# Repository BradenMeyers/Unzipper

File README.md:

# Unzipper 

These are the code files for the unzipper project. 
We have built a pully retreival sytem for a zipline that can autonomously bring the pulley back to the top of the zipline after a rider has got off the line.
The code runs on the Arduino framework and the platformIO build platform. 
The ESP32 is the microcontroller we are using to support this project. The ESP32 runs the program and hosts a server that you can connect to via WIFI to adjust settings on the system. 
It is built into a custom designed circuit that we use to control the motors, lights, and sensors.

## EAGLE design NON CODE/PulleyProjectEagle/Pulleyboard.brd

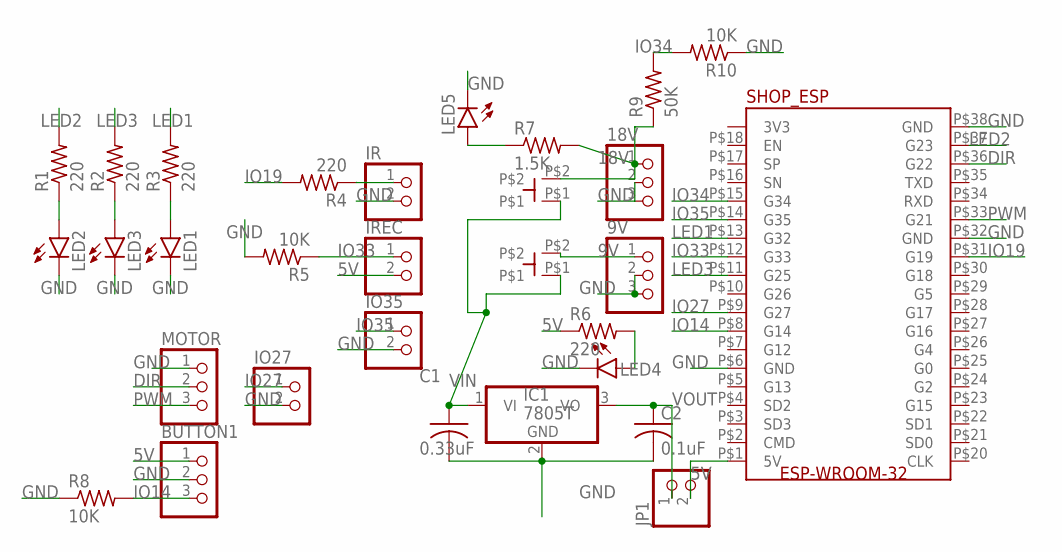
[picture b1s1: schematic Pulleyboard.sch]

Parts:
9V, 18V: PINHD-1X3; 1X03
9VSW, 18VSW: SWITCH; SWTICH
BUTTON1: PINHD-1X3; 1X03
C1: 0.33uF; C025-030X050
C2: 0.1uF; C025-030X050
IC1: 7805T; TO220H
IO27, IO35: PINHD-1X2; 1X02
IR: PINHD-1X2; 1X02
IREC: PINHD-1X2; 1X02
JP1: PINHD-1X2; 1X02
LED1, LED2, LED3, LED5: LED5MM
LED4: LEDCHIPLED_1206; CHIPLED_1206
MOTOR: PINHD-1X3; 1X03
R1, R2, R3, R4, R6: 220; R0805
R5, R8, R10: 10K; R0805
R7: 1.5K; R0805
R9: 50K; R0805
U$3: SHOP_ESP; ESP32-WROOM-32

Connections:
3V3: U$3.P$19 (3V3)
5V: BUTTON1.1, IREC.2, JP1.2, R6.1, U$3.P$1 (5V)
9V: 9V.1, 9VSW.P$2
18V: 18V.1, 18VSW.P$2, R7.2, R9.1
CMD: U$3.P$2 (CMD)
DIR: MOTOR.2, U$3.P$36 (G22)
GND: 9V.2, 9V.3, 18V.2, 18V.3, BUTTON1.2, C1.2, C2.2, IC1.2 (GND), IO27.2, IO35.2, IR.2, LED1.K (C), LED2.K (C), LED3.K (C), LED4.C, LED5.K (C), MOTOR.1, R5.2, R8.1, R10.1, U$3.P$6 (GND), U$3.P$32 (GND), U$3.P$38 (GND)
IO14: BUTTON1.3, R8.2, U$3.P$8 (G14)
IO19: R4.2, U$3.P$31 (G19)
IO27: IO27.1, U$3.P$9 (G27)
IO33: IREC.1, R5.1, U$3.P$12 (G33)
IO34: R9.2, R10.2, U$3.P$15 (G34)
IO35: IO35.1, U$3.P$14 (G35)
LED1: R3.2, U$3.P$13 (G32)
LED2: R1.2, U$3.P$37 (G23)
LED3: R2.2, U$3.P$11 (G25)
unnamed: LED2.A, R1.1
unnamed: LED3.A, R2.1
unnamed: LED1.A, R3.1
unnamed: LED5.A, R7.1
unnamed: IR.1, R4.1
unnamed: LED4.A, R6.2
PWM: MOTOR.3, U$3.P$33 (G21)
VIN: 9VSW.P$1, 18VSW.P$1, C1.1, IC1.1 (VI)
VOUT: C2.1, IC1.3 (VO), JP1.1

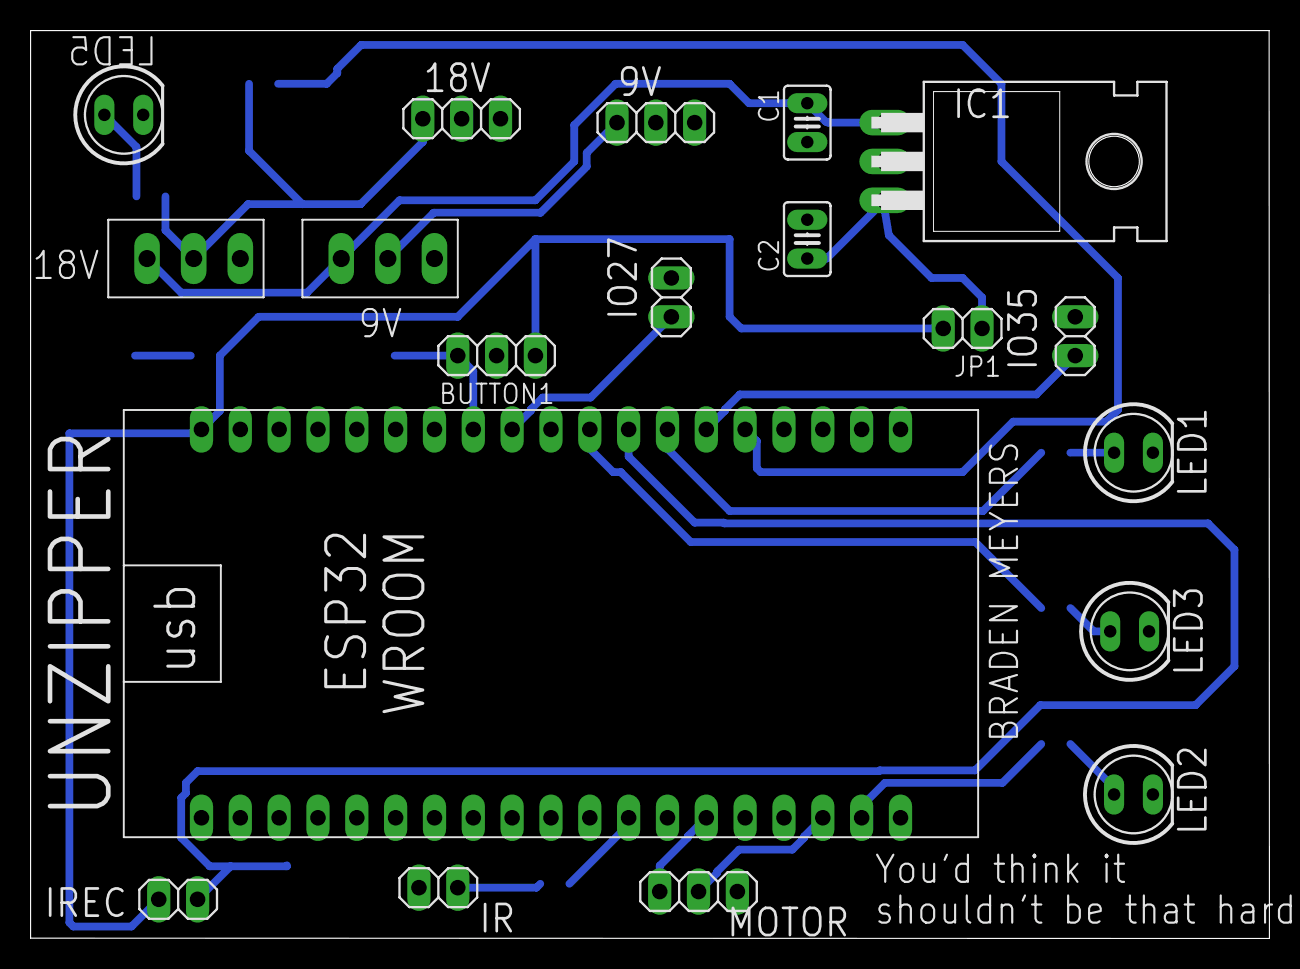
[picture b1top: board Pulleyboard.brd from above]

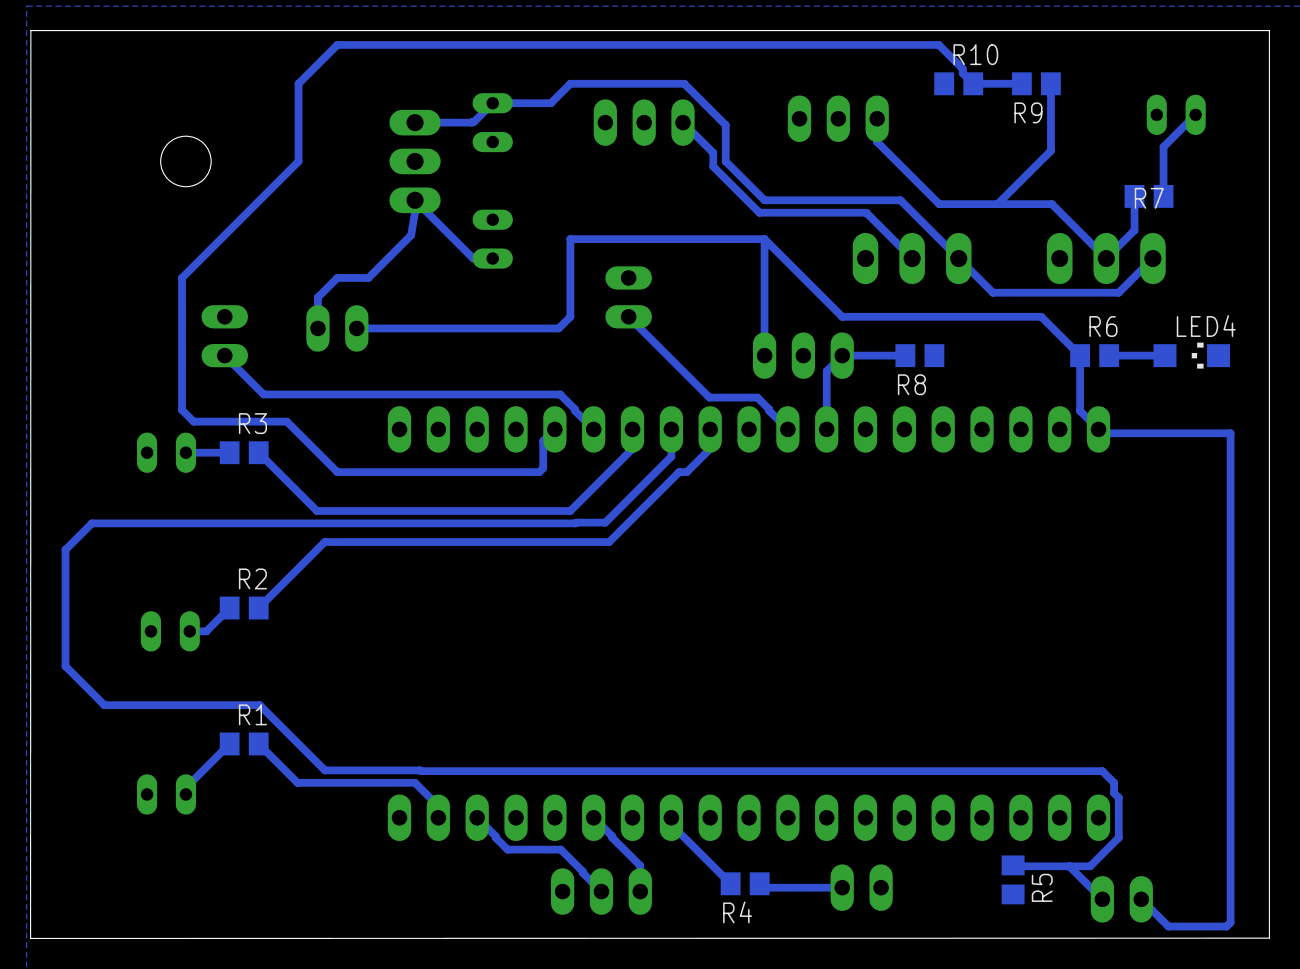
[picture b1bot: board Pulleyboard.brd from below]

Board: 2 copper layers, 81.0 x 59.4 mm, 30 parts (11 on the bottom side), 23 nets.

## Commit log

2022-11-26 Working code! Seperate files
2022-12-04 added cad files
2022-12-04 photos of cicruit board
2022-12-12 working remote controll ayay
2022-12-19 more remote functions
2022-12-22 remote with racecar mode
2023-03-14 pre website changes
2023-03-14 New Tests, Webiste, accelormeter
2023-03-17 accelerometer with Stability
2023-03-17 More server accel
2023-03-19 Servo was breaking the motor
2023-05-08 added brake file
2023-05-08 unstable stop while moving and Servo Brake
2023-05-09 updated brake
2023-05-11 Working test cases
2023-05-15 Mostly working. Small bug in stable
2023-05-22 Backup odometer
2023-05-24 odometer working. settings from website to adjust
2023-05-24 goodnightt cruel world i hate std::string
2023-07-03 gps start
2023-07-03 Kinley Commit
2023-07-03 hello
2023-07-05 gps distance between working
2023-07-11 last commit before brushless branch
2023-07-11 BLDC microsecond pwm
2023-07-11 gonna take out ramp
2023-10-23 Not sure what these changes are
2024-01-24 updates From braden
2024-01-25 I need to fix this GPS thing
2024-02-04 autonomous mode first try
2024-02-05 working auto mode
2024-02-05 first push
2024-02-12 menu and buttons
2024-02-13 Just before the new motor driver
2024-02-13 workingcode
2024-02-13 turnedoffgps
